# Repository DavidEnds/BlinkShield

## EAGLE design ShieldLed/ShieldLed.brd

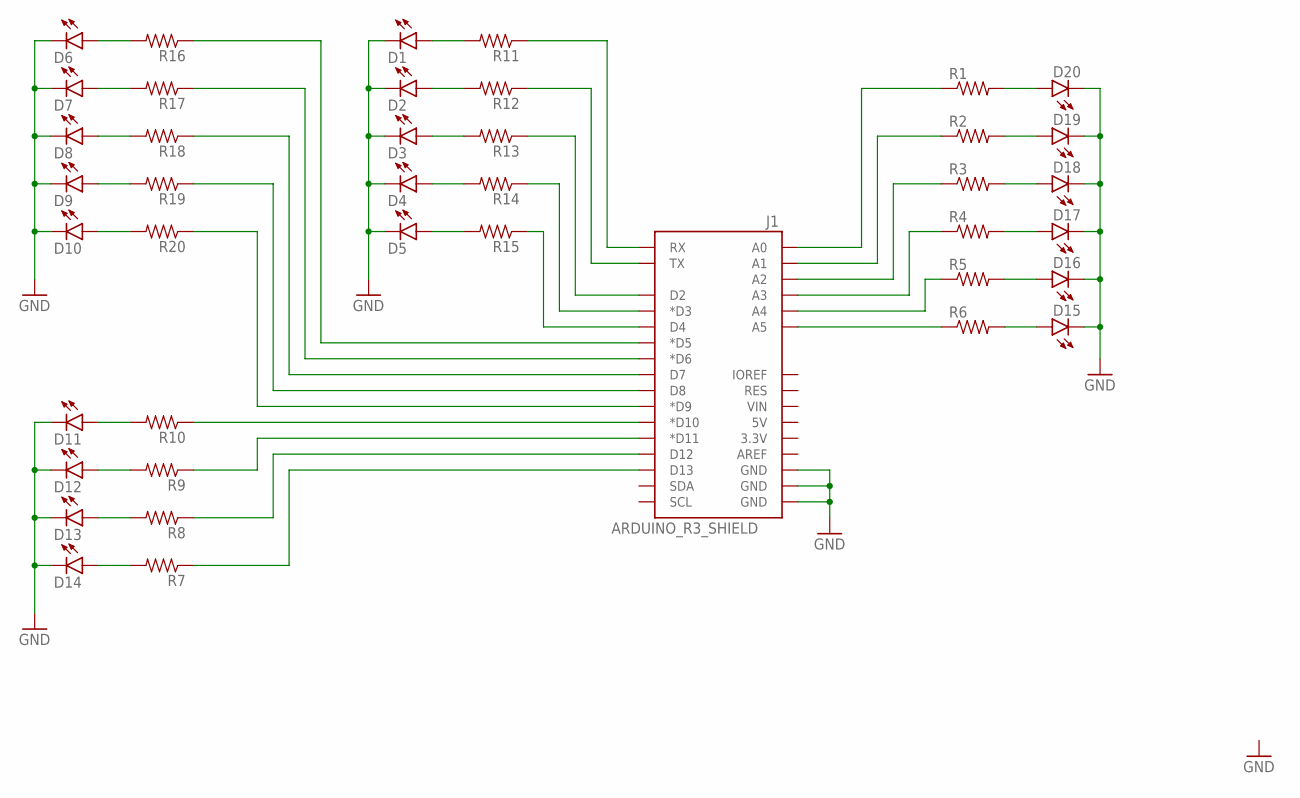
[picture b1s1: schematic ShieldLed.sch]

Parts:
D1, D2, D3, D4, D5, D6, D7, D8, D9, D10, D11, D12, D13, D14, D15, D16, D17, D18, D19, D20: LED1206; LED-1206
J1: ARDUINO_R3_SHIELD; UNO_R3_SHIELD
R1, R2, R3, R4, R5, R6, R7, R8, R9, R10, R11, R12, R13, R14, R15, R16, R17, R18, R19, R20: RESISTOR1206; 1206

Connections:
GND: D1.C, D2.C, D3.C, D4.C, D5.C, D6.C, D7.C, D8.C, D9.C, D10.C, D11.C, D12.C, D13.C, D14.C, D15.C, D16.C, D17.C, D18.C, D19.C, D20.C, J1.GND@0 (GND), J1.GND@1 (GND), J1.GND@2 (GND)
unnamed: D10.A, R20.2
unnamed: D9.A, R19.2
unnamed: D8.A, R18.2
unnamed: D7.A, R17.2
unnamed: D6.A, R16.2
unnamed: D5.A, R15.2
unnamed: D4.A, R14.2
unnamed: D3.A, R13.2
unnamed: D2.A, R12.2
unnamed: D1.A, R11.2
unnamed: D11.A, R10.2
unnamed: D12.A, R9.2
unnamed: D13.A, R8.2
unnamed: D14.A, R7.2
unnamed: D15.A, R6.2
unnamed: D16.A, R5.2
unnamed: D17.A, R4.2
unnamed: D18.A, R3.2
unnamed: D19.A, R2.2
unnamed: D20.A, R1.2
unnamed: J1.D10 (*D10), R10.1
unnamed: J1.D11 (*D11), R9.1
unnamed: J1.RX, R11.1
unnamed: J1.TX, R12.1
unnamed: J1.D2, R13.1
unnamed: J1.D3 (*D3), R14.1
unnamed: J1.D4, R15.1
unnamed: J1.D5 (*D5), R16.1
unnamed: J1.D6 (*D6), R17.1
unnamed: J1.D7, R18.1
unnamed: J1.D8, R19.1
unnamed: J1.D9 (*D9), R20.1
unnamed: J1.D12, R8.1
unnamed: J1.D13, R7.1
unnamed: J1.A5, R6.1
unnamed: J1.A4, R5.1
unnamed: J1.A3, R4.1
unnamed: J1.A2, R3.1
unnamed: J1.A1, R2.1
unnamed: J1.A0, R1.1

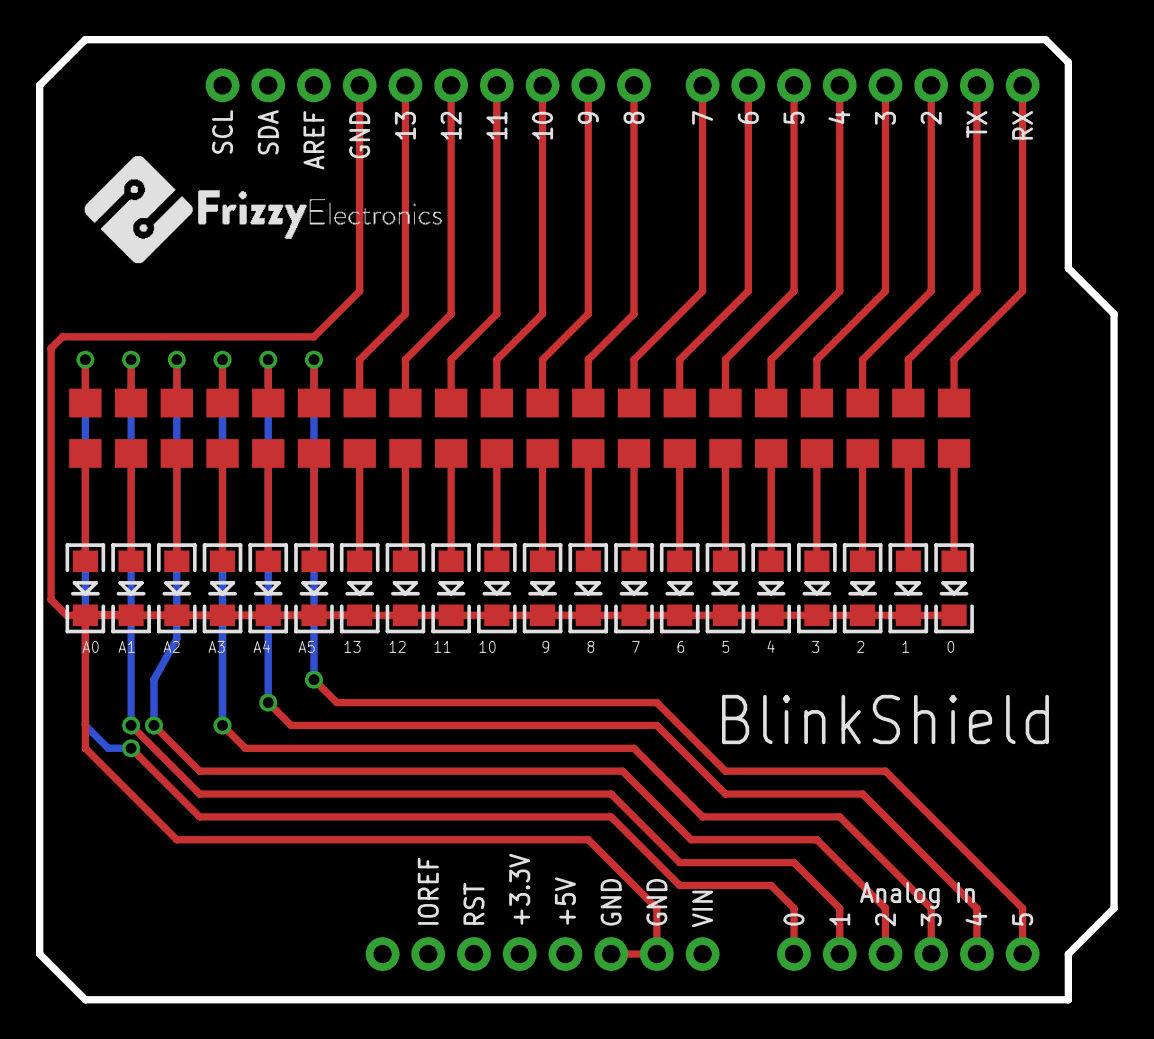
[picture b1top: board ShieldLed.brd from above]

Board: 2 copper layers, 59.7 x 53.3 mm, 41 parts (0 on the bottom side), 41 nets.

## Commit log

2016-11-19 Placa mandada a fabrica

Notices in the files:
parts and their libraries:
SparkFun-LED: Licensing: Creative Commons ShareAlike 4.0 International - https://creativecommons.org/licenses/by-sa/4.0
